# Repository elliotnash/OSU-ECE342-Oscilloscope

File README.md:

View this project on [CADLAB.io](https://cadlab.io/project/29860). 

# RustScope

A Dual Channel USB Oscilloscope designed for OSU ECE342 Junior Design 2

## Project Structure

- **`hardware/`** - Contains KiCad schematic and PCB design files for a RP2350 based oscilloscope board.

- **`firmware/`** - Rust firmware that runs on the oscilloscope board. Built using the Embassy async framework for embedded systems, targeting the RP2350 microcontroller. Handles ADC sampling / USB communication.

- **`client/`** - Tauri desktop application providing the oscilloscope user interface. Frontend built with React, TypeScript, and Tailwind CSS. Communicates with the firmware over USB to display waveforms and control oscilloscope settings.

- **`common/`** - Shared Rust crate containing models and (de)serialization logic used for communication between the firmware and Tauri application.

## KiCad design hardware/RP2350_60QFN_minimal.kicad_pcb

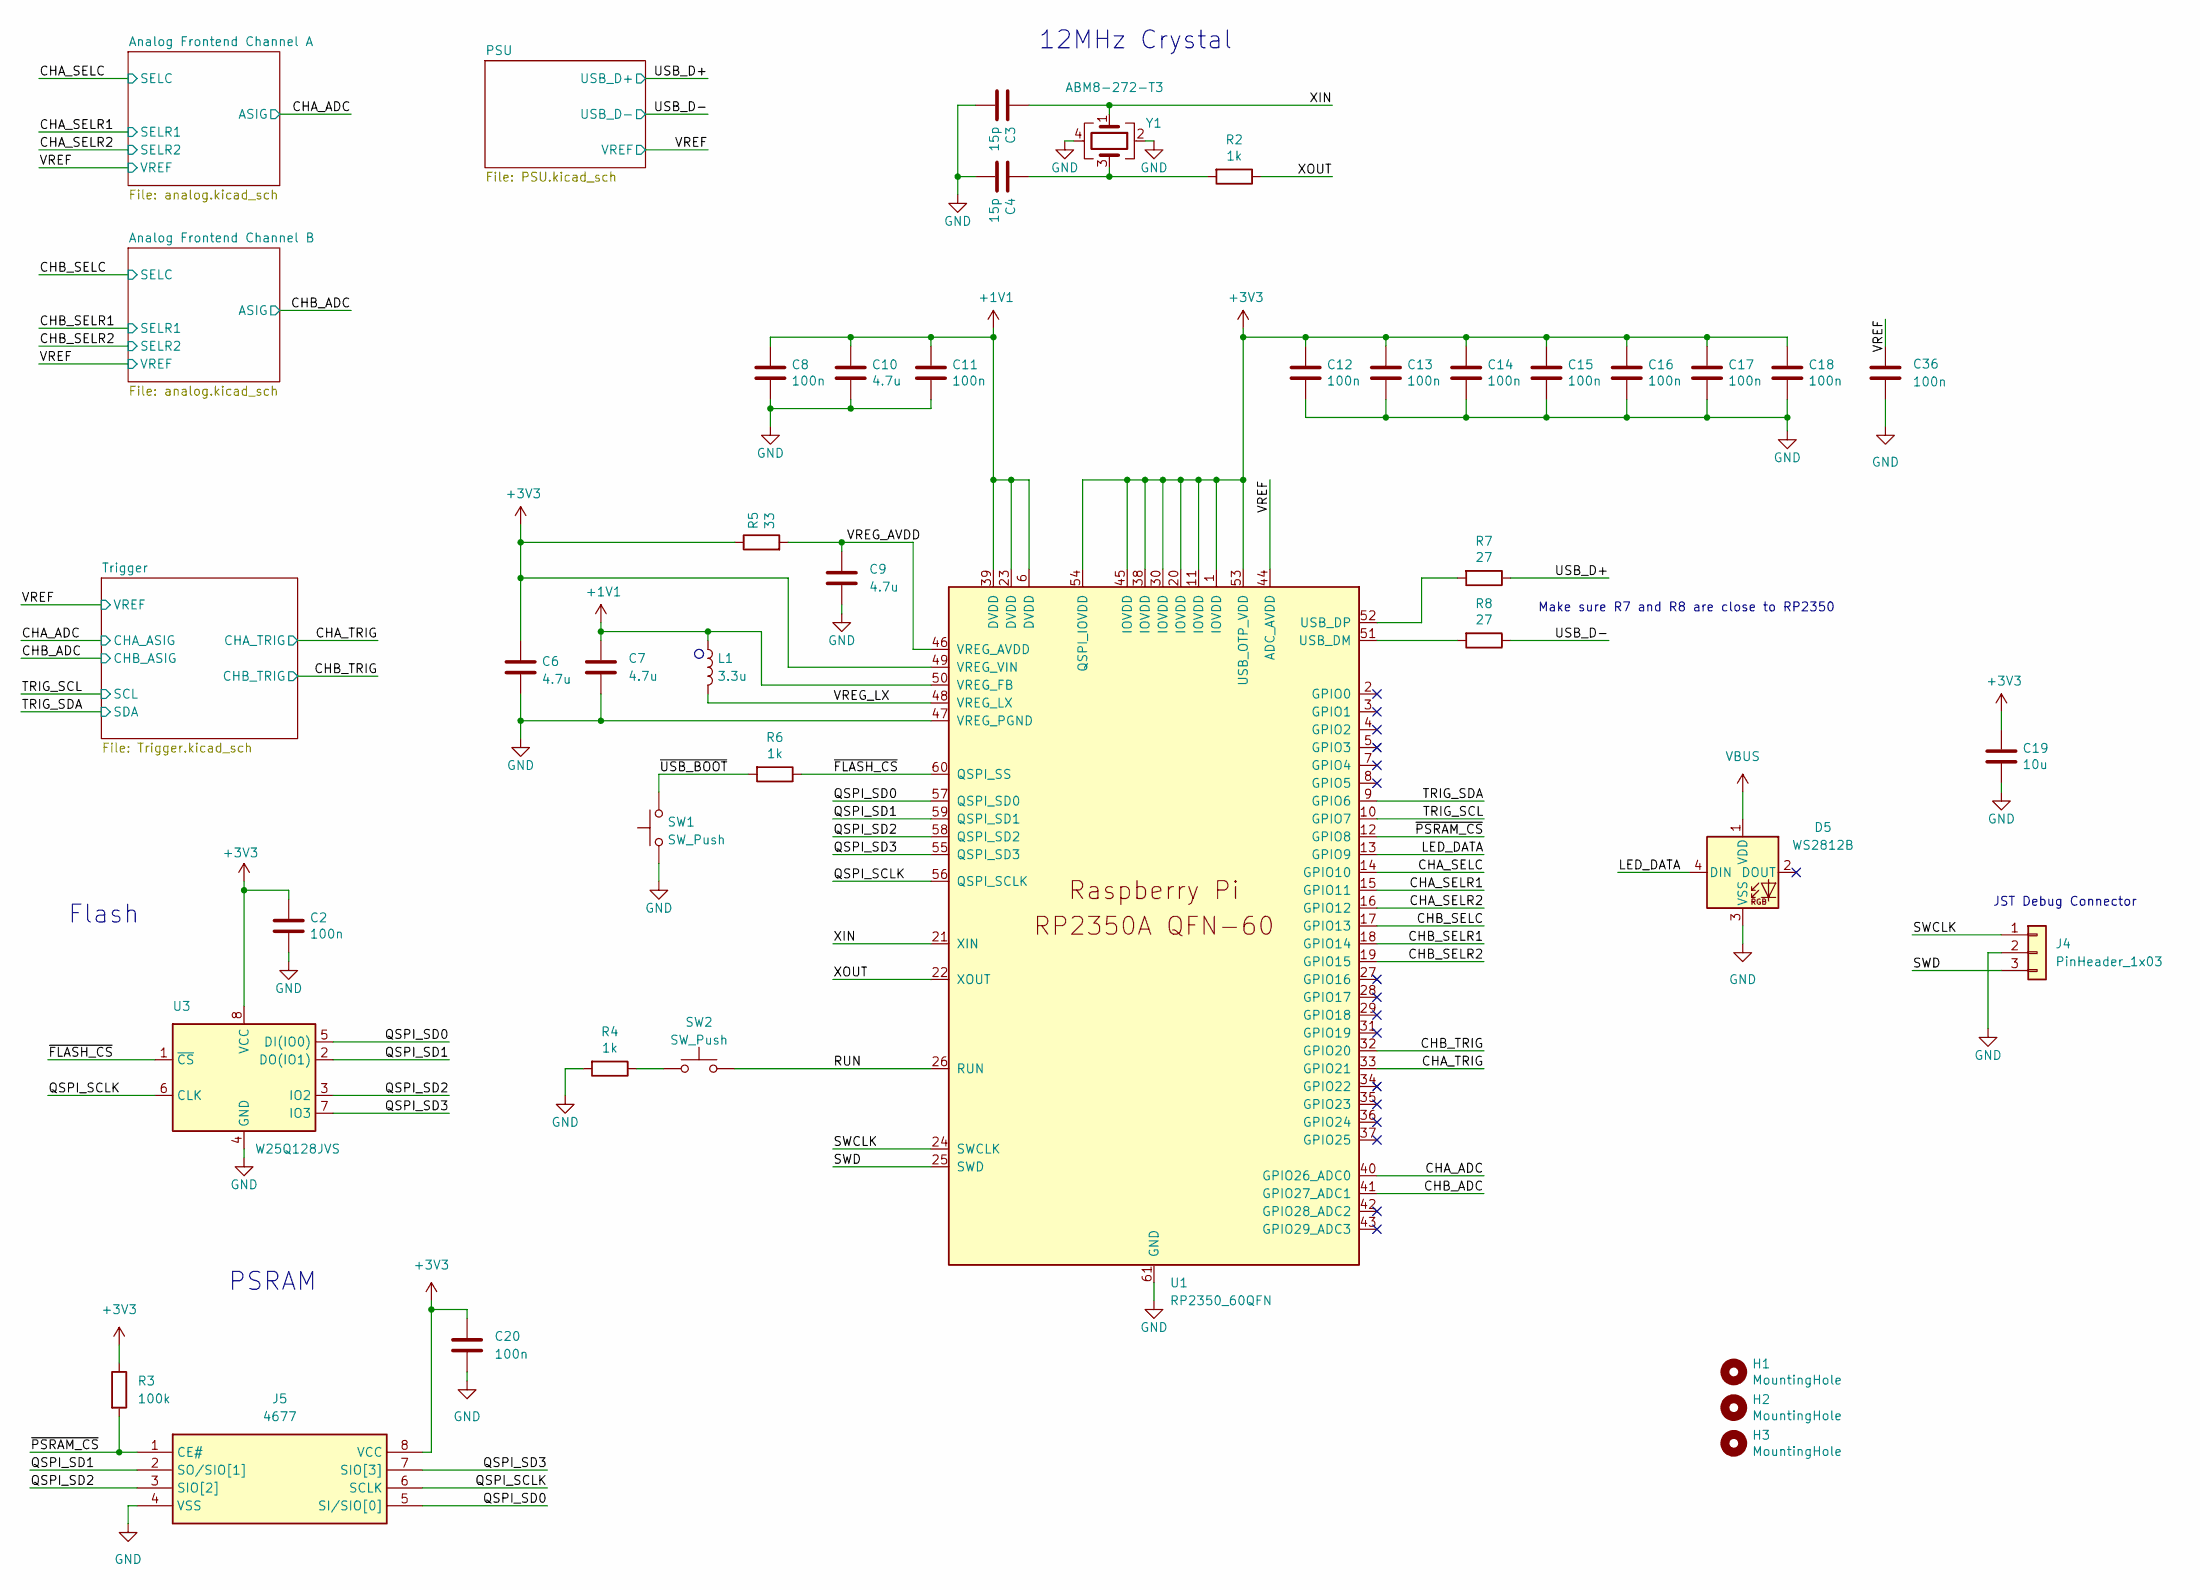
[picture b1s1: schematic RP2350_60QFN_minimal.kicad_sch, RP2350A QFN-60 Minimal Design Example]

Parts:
C2, C8, C11, C12, C13, C14, C15, C16, C17, C18, C20, C36: 100n; C_0402_1005Metric
C3, C4: 15p; C_0402_1005Metric
C6, C7: 4.7u; C_0402_1005Metric_small_pads
C9, C10: 4.7u; C_0402_1005Metric
C19: 10u; C_0805_2012Metric
D5: WS2812B; LED_WS2812B-Mini_PLCC4_3.5x3.5mm
H1, H2, H3: MountingHole; MountingHole_2.7mm_M2.5
J4: PinHeader_1x03; PinHeader_1x03_P2.54mm_Vertical
J5: 4677; SOIC127P600X175-8N; Mouser Part Number 485-4677
L1: 3.3u; L_pol_2016
R2, R4, R6: 1k; R_0402_1005Metric
R3: 100k; R_0402_1005Metric
R5: 33; R_0402_1005Metric
R7, R8: 27; R_0402_1005Metric
SW1, SW2: SW_Push; SW_TL3365AF180QG
U1: RP2350_60QFN; RP2350-QFN-60-1EP_7x7_P0.4mm_EP3.4x3.4mm_ThermalVias
U3: W25Q128JVS; SOIC-8_5.23x5.23mm_P1.27mm
Y1: ABM8-272-T3; Crystal_SMD_3225-4Pin_3.2x2.5mm

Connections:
+1V1: C7.1, C8.1, C10.1, C11.1, L1.1, U1.6 (DVDD), U1.23 (DVDD), U1.39 (DVDD), U1.50 (VREG_FB)
+3V3: C2.1, C6.1, C12.1, C13.1, C14.1, C15.1, C16.1, C17.1, C18.1, C19.1, C20.1, J5.8 (VCC), R3.1, R5.1, U1.1 (IOVDD), U1.11 (IOVDD), U1.20 (IOVDD), U1.30 (IOVDD), U1.38 (IOVDD), U1.45 (IOVDD), U1.49 (VREG_VIN), U1.53 (USB_OTP_VDD), U1.54 (QSPI_IOVDD), U3.8 (VCC); also elsewhere on the board
/CHA_ADC: U1.40 (GPIO26_ADC0); also elsewhere on the board
/CHA_SELC: U1.14 (GPIO10); also elsewhere on the board
/CHA_SELR1: U1.15 (GPIO11); also elsewhere on the board
/CHA_SELR2: U1.16 (GPIO12); also elsewhere on the board
/CHA_TRIG: U1.33 (GPIO21); also elsewhere on the board
/CHB_ADC: U1.41 (GPIO27_ADC1); also elsewhere on the board
/CHB_SELC: U1.17 (GPIO13); also elsewhere on the board
/CHB_SELR1: U1.18 (GPIO14); also elsewhere on the board
/CHB_SELR2: U1.19 (GPIO15); also elsewhere on the board
/CHB_TRIG: U1.32 (GPIO20); also elsewhere on the board
/LED_DATA: D5.4 (DIN), U1.13 (GPIO9)
/QSPI_SCLK: J5.6 (SCLK), U1.56 (QSPI_SCLK), U3.6 (CLK)
/QSPI_SD0: J5.5 (SI/SIO[0]), U1.57 (QSPI_SD0), U3.5 (DI(IO0))
/QSPI_SD1: J5.2 (SO/SIO[1]), U1.59 (QSPI_SD1), U3.2 (DO(IO1))
/QSPI_SD2: J5.3 (SIO[2]), U1.58 (QSPI_SD2), U3.3 (IO2)
/QSPI_SD3: J5.7 (SIO[3]), U1.55 (QSPI_SD3), U3.7 (IO3)
/RUN: SW2.2, U1.26 (RUN)
/SWCLK: J4.1, U1.24 (SWCLK)
/SWD: J4.3, U1.25 (SWD)
/TRIG_SCL: U1.10 (GPIO7); also elsewhere on the board
/TRIG_SDA: U1.9 (GPIO6); also elsewhere on the board
/USB_D+: R7.1; also elsewhere on the board
/USB_D-: R8.1; also elsewhere on the board
/VREF: C36.1, U1.44 (ADC_AVDD); also elsewhere on the board
/VREG_AVDD: C9.1, R5.2, U1.46 (VREG_AVDD)
/VREG_LX: L1.2, U1.48 (VREG_LX)
/XIN: C3.1, U1.21 (XIN), Y1.1
/XOUT: R2.1, U1.22 (XOUT)
/~FLASH_CS: R6.1, U1.60 (QSPI_SS), U3.1 (~CS)
/~PSRAM_CS: J5.1 (CE#), R3.2, U1.12 (GPIO8)
/~USB_BOOT: R6.2, SW1.2
GND: C2.2, C3.2, C4.2, C6.2, C7.2, C8.2, C9.2, C10.2, C11.2, C12.2, C13.2, C14.2, C15.2, C16.2, C17.2, C18.2, C19.2, C20.2, C36.2, D5.3 (VSS), J4.2, J5.4 (VSS), R4.2, SW1.1, U1.47 (VREG_PGND), U1.61 (GND), U3.4 (GND), Y1.2, Y1.4; also elsewhere on the board
unnamed: C4.1, R2.2, Y1.3
unnamed: R4.1, SW2.1
unnamed: R8.2, U1.51 (USB_DM)
unnamed: R7.2, U1.52 (USB_DP)
VBUS: D5.1 (VDD); also elsewhere on the board

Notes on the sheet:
JST Debug Connector
Flash
Make sure R7 and R8 are close to RP2350
PSRAM
12MHz Crystal

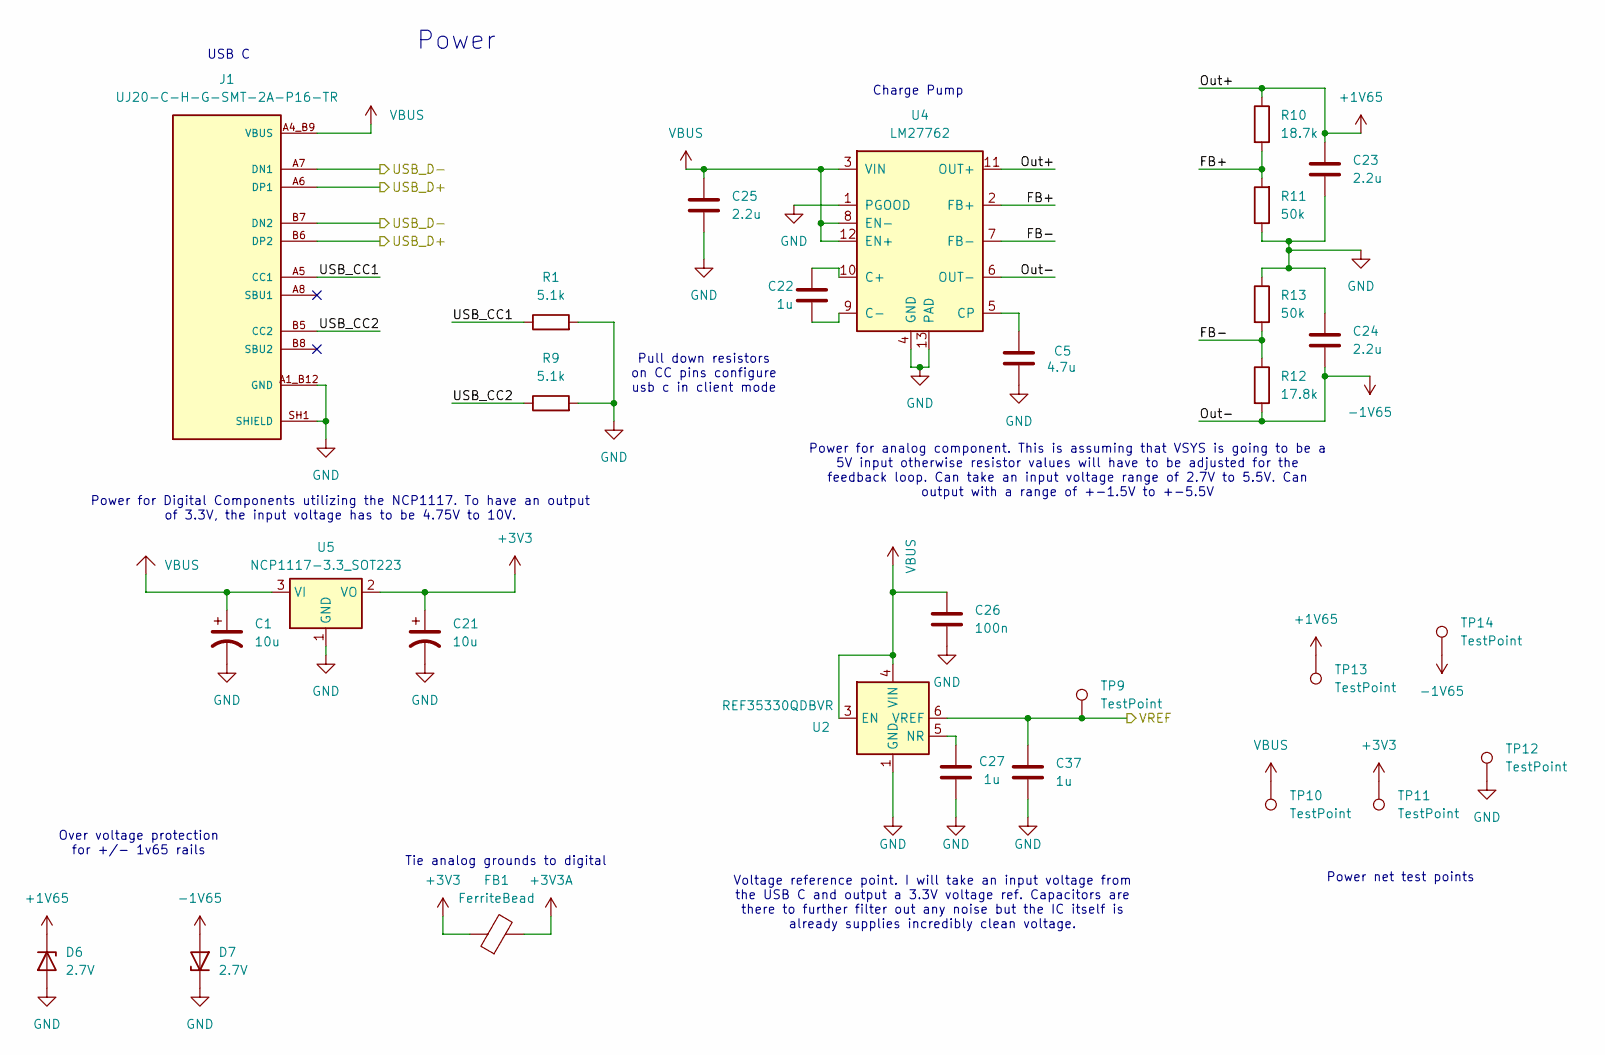
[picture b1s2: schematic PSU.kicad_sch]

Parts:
C1, C21: 10u; C_1206_3216Metric
C5: 4.7u; C_0402_1005Metric
C22, C27, C37: 1u; C_0402_1005Metric
C23, C24, C25: 2.2u; C_0402_1005Metric
C26: 100n; C_0402_1005Metric
D6, D7: 2.7V; D_SOD-123
FB1: FerriteBead; R_0603_1608Metric
J1: UJ20-C-H-G-SMT-2A-P16-TR; SAMESKY_UJ20-C-H-G-SMT-1-P16-TR; PARTREV 1.0
R1, R9: 5.1k; R_0402_1005Metric
R10: 18.7k; R_0402_1005Metric
R11, R13: 50k; R_0402_1005Metric
R12: 17.8k; R_0402_1005Metric
TP9, TP10, TP11, TP12, TP13, TP14: TestPoint; TestPoint_0603_1608Metric
U2: REF35330QDBVR; SOT-23-6
U4: LM27762; WSON-12-1EP_3x2mm_P0.5mm_EP1x2.65_ThermalVias
U5: NCP1117-3.3_SOT223; SOT-223-3_TabPin2

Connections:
+1V65: C23.1, D6.1 (K), R10.1, TP13.1, U4.11 (OUT+); also elsewhere on the board
+3V3: C21.1, FB1.1, TP11.1, U5.2 (VO); also elsewhere on the board
+3V3A: FB1.2; also elsewhere on the board
-1V65: C24.1, D7.2 (A), R12.2, TP14.1, U4.6 (OUT-); also elsewhere on the board
/PSU/FB+: R10.2, R11.2, U4.2 (FB+)
/PSU/FB-: R12.1, R13.2, U4.7 (FB-)
/PSU/USB_CC1: J1.A5 (CC1), R1.1
/PSU/USB_CC2: J1.B5 (CC2), R9.1
/USB_D+: J1.A6 (DP1), J1.B6 (DP2); also elsewhere on the board
/USB_D-: J1.A7 (DN1), J1.B7 (DN2); also elsewhere on the board
/VREF: C37.1, TP9.1, U2.6 (VREF); also elsewhere on the board
GND: C1.2, C5.2, C21.2, C23.2, C24.2, C25.2, C26.2, C27.1, C37.2, D6.2 (A), D7.1 (K), J1.A1_B12 (GND), J1.B1_A12 (GND), J1.SH1 (SHIELD), J1.SH2 (SHIELD), J1.SH3 (SHIELD), J1.SH4 (SHIELD), R1.2, R9.2, R11.1, R13.1, TP12.1, U2.1 (GND), U2.2 (GND), U4.1 (PGOOD), U4.4 (GND), U4.13 (PAD), U5.1 (GND); also elsewhere on the board
unnamed: C27.2, U2.5 (NR)
unnamed: C22.1, U4.10 (C+)
unnamed: C22.2, U4.9 (C-)
unnamed: C5.1, U4.5 (CP)
VBUS: C1.1, C25.1, C26.1, J1.A4_B9 (VBUS), J1.B4_A9 (VBUS), TP10.1, U2.3 (EN), U2.4 (VIN), U4.3 (VIN), U4.8 (EN-), U4.12 (EN+), U5.3 (VI); also elsewhere on the board

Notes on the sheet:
Pull down resistors on CC pins configure usb c in client mode
Charge Pump
USB C
Power for analog component. This is assuming that VSYS is going to be a 5V input otherwise resistor values will have to be adjusted for the feedback loop. Can take an input voltage range of 2.7V to 5.5V. Can output with a range of +-1.5V to +-5.5V
Power net test points
Power for Digital Components utilizing the NCP1117. To have an output of 3.3V, the input voltage has to be 4.75V to 10V.
Tie analog grounds to digital
Voltage reference point. I will take an input voltage from the USB C and output a 3.3V voltage ref. Capacitors are there to further filter out any noise but the IC itself is already supplies incredibly clean voltage.
Over voltage protection for +/- 1v65 rails
Power

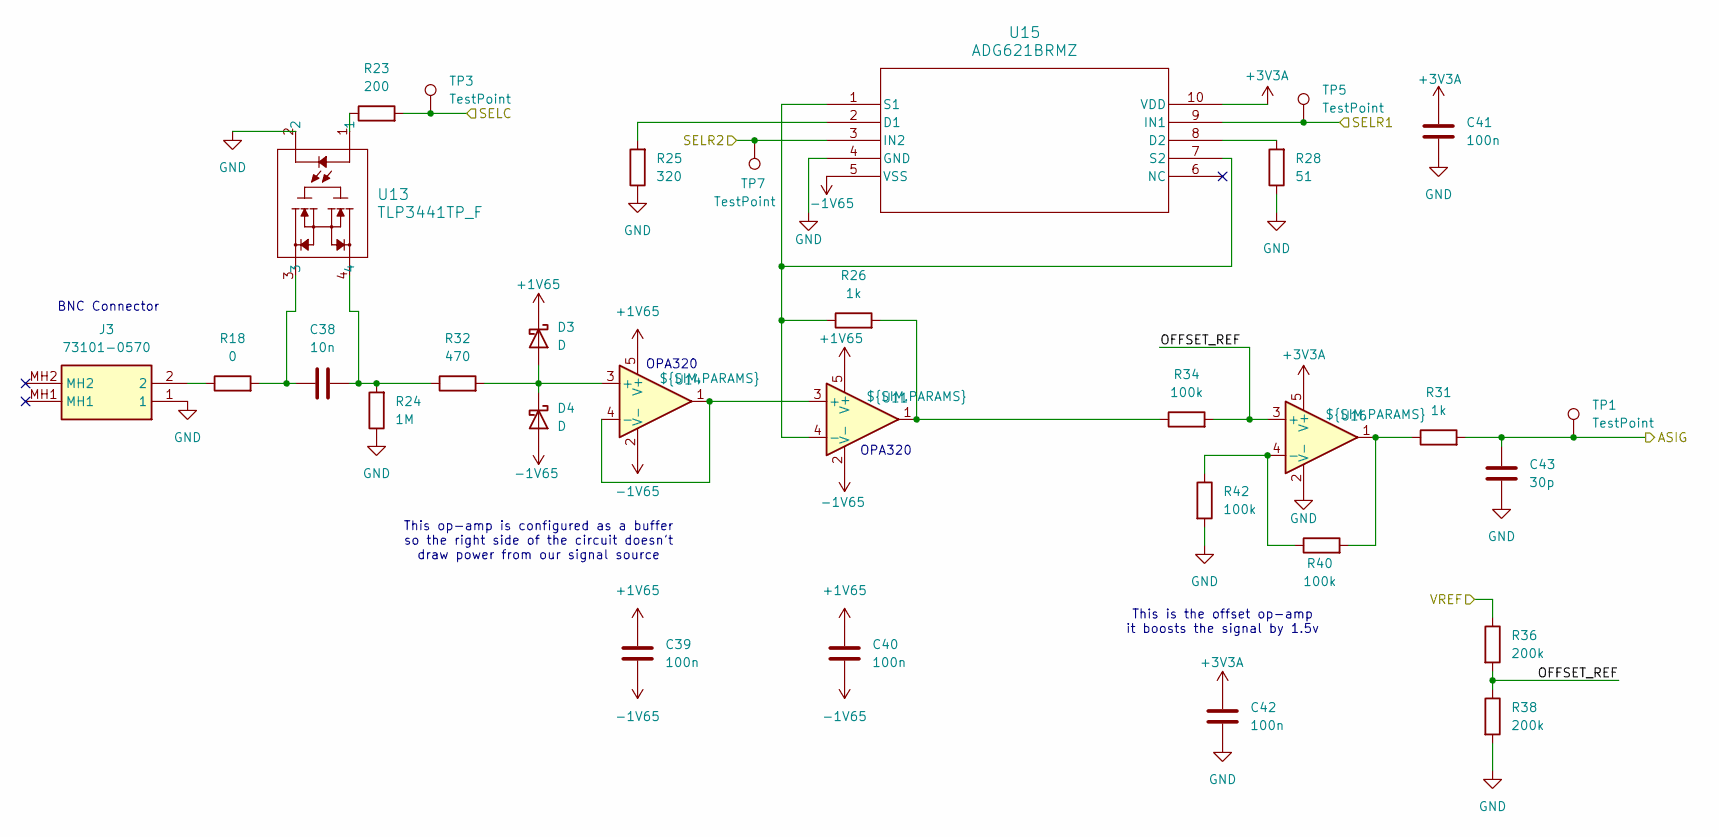
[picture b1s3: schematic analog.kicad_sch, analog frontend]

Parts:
C38: 10n; C_0402_1005Metric
C39, C40, C41, C42: 100n; C_0402_1005Metric
C43: 30p; C_0402_1005Metric
D3, D4: D; D_SOD-123
J3: 73101-0570; 731010570; Mouser Part Number 538-73101-0570
R18: 0; R_0603_1608Metric
R23: 200; R_0402_1005Metric
R24: 1M; R_0603_1608Metric
R25: 320; R_0603_1608Metric
R26, R31: 1k; R_0402_1005Metric
R28: 51; R_0603_1608Metric
R32: 470; R_0402_1005Metric
R34, R40, R42: 100k; R_0402_1005Metric
R36, R38: 200k; R_0402_1005Metric
TP1, TP3, TP5, TP7: TestPoint; TestPoint_0603_1608Metric
U11, U14, U16: ${SIM.PARAMS}; DBV5
U13: TLP3441TP_F; VSON4_TOS
U15: ADG621BRMZ; RM_10_ADI

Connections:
+1V65: C39.1, C40.1, D3.1 (K), U11.5 (V+), U14.5 (V+); also elsewhere on the board
+3V3A: C41.1, C42.1, U15.10 (VDD), U16.5 (V+); also elsewhere on the board
-1V65: C39.2, C40.2, D4.2 (A), U11.2 (V-), U14.2 (V-), U15.5 (VSS); also elsewhere on the board
/Analog Frontend Channel A/OFFSET_REF: R34.2, R36.2, R38.1, U16.3 (+)
/CHA_ADC: C43.1, R31.2, TP1.1; also elsewhere on the board
/CHA_SELC: R23.2, TP3.1; also elsewhere on the board
/CHA_SELR1: TP5.1, U15.9 (IN1); also elsewhere on the board
/CHA_SELR2: TP7.1, U15.3 (IN2); also elsewhere on the board
/VREF: R36.1; also elsewhere on the board
GND: C41.2, C42.2, C43.2, J3.1, R24.1, R25.1, R28.1, R38.2, R42.2, U13.2, U15.4 (GND), U16.2 (V-); also elsewhere on the board
unnamed: C38.1, R18.2, U13.3
unnamed: C38.2, R24.2, R32.1, U13.4
unnamed: D3.2 (A), D4.1 (K), R32.2, U14.3 (+)
unnamed: J3.2, R18.1
unnamed: R23.1, U13.1
unnamed: R26.2, R34.1, U11.1
unnamed: R31.1, R40.2, U16.1
unnamed: U11.3 (+), U14.1, U14.4 (-)
unnamed: R26.1, U11.4 (-), U15.1 (S1), U15.7 (S2)
unnamed: R25.2, U15.2 (D1)
unnamed: R28.2, U15.8 (D2)
unnamed: R40.1, R42.1, U16.4 (-)

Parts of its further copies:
C29: 10n; C_0402_1005Metric
C31, C32, C33, C34: 100n; C_0402_1005Metric
C35: 30p; C_0402_1005Metric
D1, D2: D; D_SOD-123
J2: 73101-0570; 731010570; Mouser Part Number 538-73101-0570
R14: 200; R_0402_1005Metric
R15: 1M; R_0603_1608Metric
R16: 320; R_0603_1608Metric
R17, R22: 1k; R_0402_1005Metric
R19: 51; R_0603_1608Metric
R20: 0; R_0603_1608Metric
R33: 470; R_0402_1005Metric
R35, R41, R43: 100k; R_0402_1005Metric
R37, R39: 200k; R_0402_1005Metric
TP2, TP4, TP6, TP8: TestPoint; TestPoint_0603_1608Metric
U8: TLP3441TP_F; VSON4_TOS
U10: ADG621BRMZ; RM_10_ADI

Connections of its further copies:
+1V65: C31.1, C32.1, D1.1 (K); also elsewhere on the board
+3V3A: C33.1, C34.1, U10.10 (VDD); also elsewhere on the board
-1V65: C31.2, C32.2, D2.2 (A), U10.5 (VSS); also elsewhere on the board
/Analog Frontend Channel B/OFFSET_REF: R35.2, R37.2, R39.1; also elsewhere on the board
/CHB_ADC: C35.1, R22.2, TP2.1; also elsewhere on the board
/CHB_SELC: R14.2, TP4.1; also elsewhere on the board
/CHB_SELR1: TP6.1, U10.9 (IN1); also elsewhere on the board
/CHB_SELR2: TP8.1, U10.3 (IN2); also elsewhere on the board
/VREF: R37.1; also elsewhere on the board
GND: C33.2, C34.2, C35.2, J2.1, R15.1, R16.1, R19.1, R39.2, R43.2, U8.2, U10.4 (GND); also elsewhere on the board
unnamed: C29.1, R20.2, U8.3
unnamed: C29.2, R15.2, R33.1, U8.4
unnamed 50: D1.2 (A), D2.1 (K), R33.2; also elsewhere on the board
unnamed: J2.2, R20.1
unnamed: R14.1, U8.1
unnamed 56: R17.2, R35.1; also elsewhere on the board
unnamed 57: R22.1, R41.2; also elsewhere on the board
unnamed: R16.2, U10.2 (D1)
unnamed: R19.2, U10.8 (D2)
unnamed 71: R17.1, U10.1 (S1), U10.7 (S2); also elsewhere on the board
unnamed 78: R41.1, R43.1; also elsewhere on the board

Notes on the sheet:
OPA320
BNC Connector
This op-amp is configured as a buffer so the right side of the circuit doesn't draw power from our signal source
This is the offset op-amp it boosts the signal by 1.5v

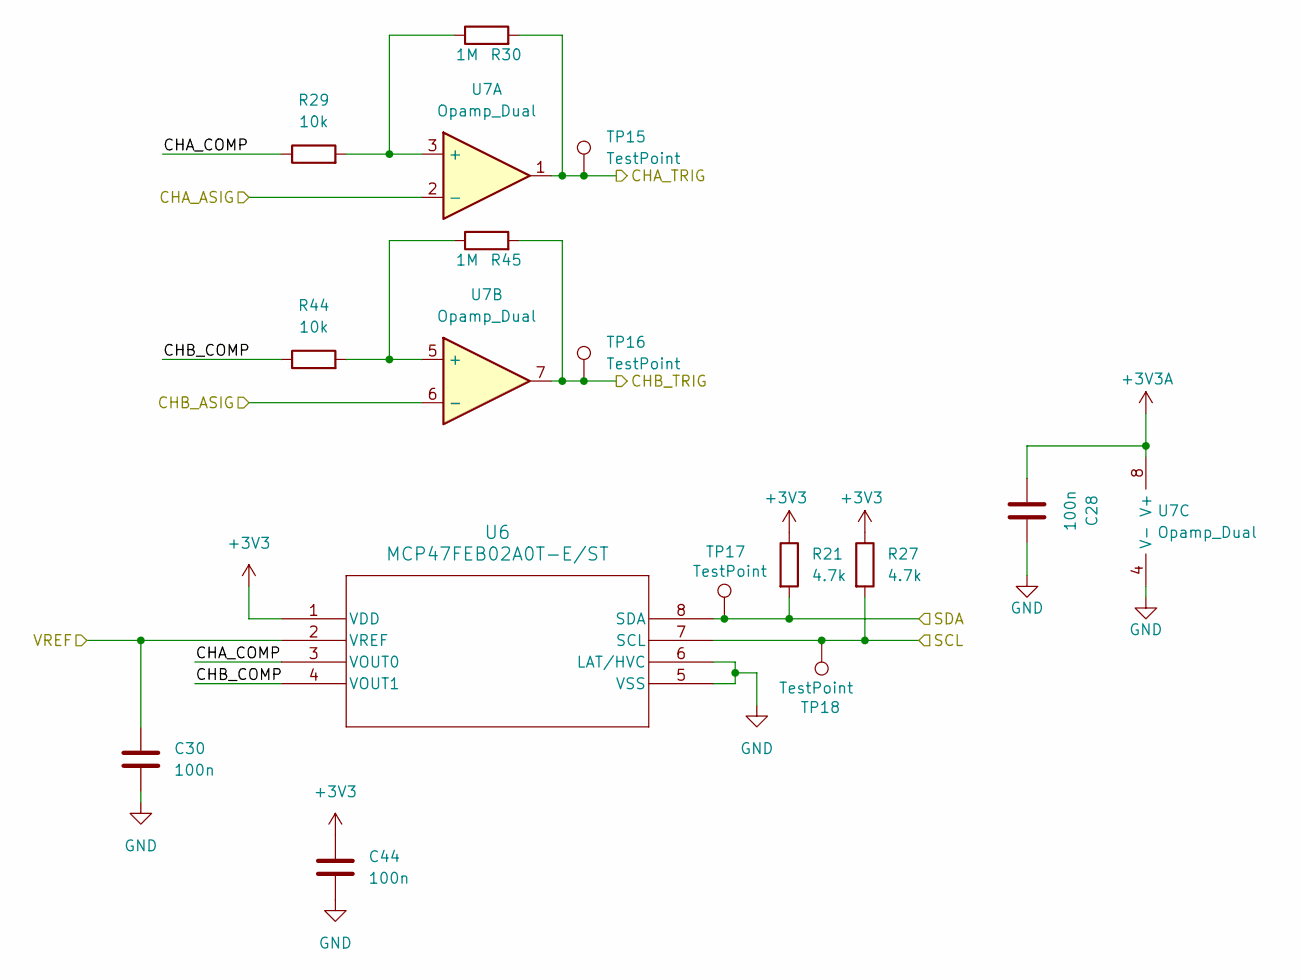
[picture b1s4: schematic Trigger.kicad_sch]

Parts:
C28, C30, C44: 100n; C_0402_1005Metric
R21, R27: 4.7k; R_0402_1005Metric
R29, R44: 10k; R_0402_1005Metric
R30, R45: 1M; R_0402_1005Metric
TP15, TP16, TP17, TP18: TestPoint; TestPoint_0603_1608Metric
U6: MCP47FEB02A0T-E/ST; TSSOP8_ST_MCH
U7: Opamp_Dual; SOIC127P600X175-8N

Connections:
+3V3: C44.2, R21.1, R27.1, U6.1 (VDD); also elsewhere on the board
+3V3A: C28.1, U7.8 (V+); also elsewhere on the board
/CHA_ADC: U7.2 (-); also elsewhere on the board
/CHA_TRIG: R30.2, TP15.1, U7.1; also elsewhere on the board
/CHB_ADC: U7.6 (-); also elsewhere on the board
/CHB_TRIG: R45.2, TP16.1, U7.7; also elsewhere on the board
/TRIG_SCL: R27.2, TP18.1, U6.7 (SCL); also elsewhere on the board
/TRIG_SDA: R21.2, TP17.1, U6.8 (SDA); also elsewhere on the board
/Trigger/CHA_COMP: R29.1, U6.3 (VOUT0)
/Trigger/CHB_COMP: R44.1, U6.4 (VOUT1)
/VREF: C30.2, U6.2 (VREF); also elsewhere on the board
GND: C28.2, C30.1, C44.1, U6.5 (VSS), U6.6 (LAT/HVC), U7.4 (V-); also elsewhere on the board
unnamed: R29.2, R30.1, U7.3 (+)
unnamed: R44.2, R45.1, U7.5 (+)

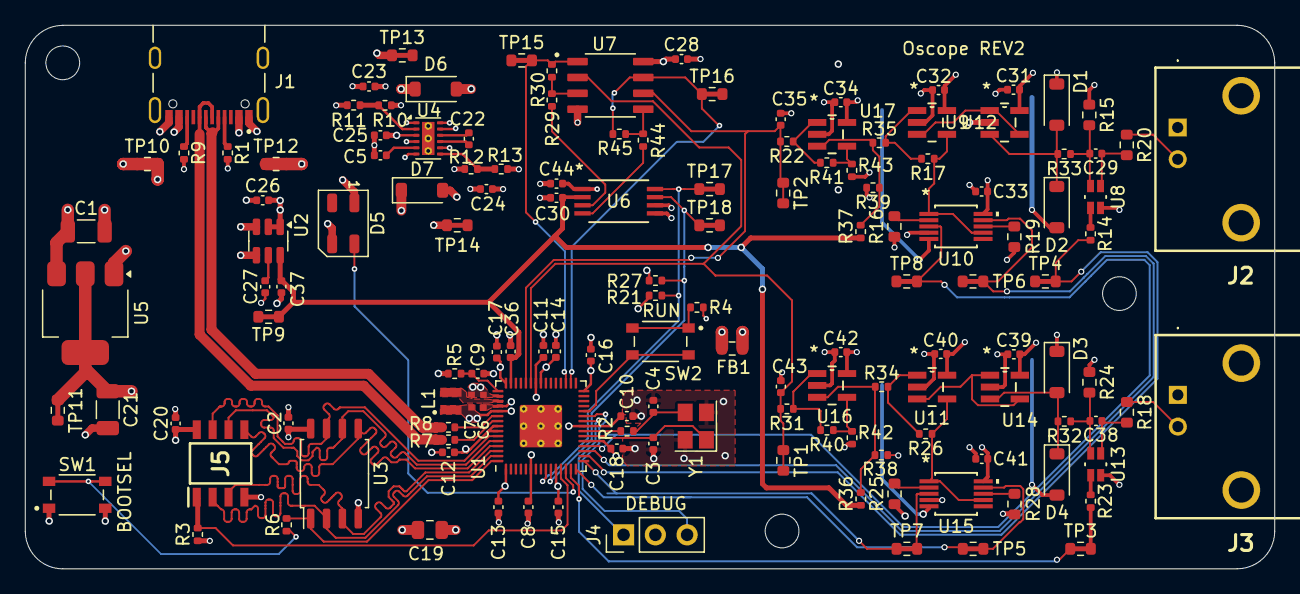
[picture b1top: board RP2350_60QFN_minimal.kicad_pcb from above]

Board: 4 copper layers, 100.0 x 43.5 mm, 144 parts (0 on the bottom side), 80 nets.

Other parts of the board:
U9, U12, U17: DBV5

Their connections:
+1V65: U9.5 (V+), U12.5 (V+); also elsewhere on the board
+3V3A: U17.5 (V+); also elsewhere on the board
-1V65: U9.2 (V-), U12.2 (V-); also elsewhere on the board
/Analog Frontend Channel B/OFFSET_REF: U17.3 (+); also elsewhere on the board
GND: U17.2 (V-); also elsewhere on the board
unnamed 50: U9.3 (+); also elsewhere on the board
unnamed 56: U12.1; also elsewhere on the board
unnamed 57: U17.1; also elsewhere on the board
unnamed 71: U12.4 (-); also elsewhere on the board
unnamed: U9.1, U9.4 (-), U12.3 (+)
unnamed 78: U17.4 (-); also elsewhere on the board

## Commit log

2026-01-16 feat: Initial per platform theming
2026-01-16 feat: Implement tauri logging
2026-01-18 Backlink to CADLAB.io has been added.
2026-01-18 replaced hardware folder with minimal simulation of rp2350
2026-01-19 feat(hardware): Add 8MB PSRAM Flash
2026-01-19 feat(hardware): Add USBC 1332645 library
2026-01-20 feat(hardware): Swap Micro USB with USB C
2026-01-20 feat(application): Prepare for move to main repository
2026-01-20 feat(client): Rename app->client
2026-01-20 feat(firmware,common): Initial firmware
2026-01-20 docs: Update readme
2026-01-20 ci(common): CI for common crate
2026-01-20 ci(common): Fix CI
2026-01-20 ci(common): Fix CI pt. 2
2026-01-20 ci(common): Update CI
2026-01-20 chore(common): Cargo fmt
2026-01-20 added digital psu
2026-01-20 added analog psu, needs review
2026-01-20 added links and prices
2026-01-21 feat(hardware): Move PSU to subschematic
2026-01-22 not done with Vref just saving for the night
2026-01-22 feat(client): Fix client builds, add CI builds
2026-01-22 ci(client): Add ubuntu dependencies
2026-01-22 ci(client): Update dependencies
2026-01-22 ci(client): Upload client bundle artifacts
2026-01-22 ci(client): Don't strip tauri builds
2026-01-22 added heirarchical labels for analog block
2026-01-22 updating
2026-01-22 merging stuff
2026-01-22 "Updated PSU, Updated spreadsheets
2026-01-23 finished part selection for analog/added photorelay switch for ac/dc coupling
2026-01-25 docs: Add initial docs
2026-01-25 docs: Update block diagram, add template for individual blocks
2026-01-26 feat(common): Add adaptive delta packing serializer for frame data
2026-01-26 feat(common): Refactor common crate
2026-01-26 fix(common): Fix improper absolute serialization of negative deltas
2026-01-26 chore(frontend,backend): Refactor client into backend/frontend directories, prepare to merge backend into cargo workspace
2026-01-26 ci(frontend,backend): Fix CI for client migration
2026-01-26 ci(application): Fix tauri cli install
2026-01-29 Up to date
2026-01-29 Trig
2026-01-29 added bnc foorptint and symbol
2026-01-29 Trig finished
2026-01-29 added decoupling capacitors to analog block
2026-01-29 updated trig
2026-01-30 connected analog i/o on main schematic and updated PSU naming
2026-01-31 feat(hardware): Cleanup schematic, replace offset stage with non-inverting op amp, add neopixel LED
2026-01-31 feat(hardware): Add charge pump over-voltage protection
2026-01-31 fix(hardware): Make power rail net naming consistent
2026-02-02 feat(frontend,backend): Migrate to IntentUI, update native colours
2026-02-02 feat(backend, frontend): Add support for platform titlebar controls
2026-02-02 chore(backend): Cargo fmt
2026-02-02 feat(hardware): Add zero ohm resistor before analog input
2026-02-03 feat(backend): Update linux theme
2026-02-03 updated psu
2026-02-04 updated spreadsheet
2026-02-04 added footprints
2026-02-04 feat(frontend): Add libadwaita style titlebar on linux
2026-02-04 feat(frontend): Add approximate macos traffic light buttons
2026-02-04 fix(frontend): Minor styling fixes
2026-02-05 feat(hardware): Add test point connections + update PCB layout
2026-02-05 feat(hardware): Update PCB layout for power and trigger blocks
2026-02-06 chore: Migrate to cargo workspace
2026-02-06 feat(test-firmware): Add initial USB-CDC test firmware
2026-02-06 feat(backend): Add serial port implementation
2026-02-06 feat(backend,frontend): Migrate to tanstack router, add USB connection logic in frontend
2026-02-07 feat(backend,frontend): Working mcu<->backend comm
2026-02-07 feat(backend): Use tokio channel for status
2026-02-07 feat(hardware): Organize MCU block layout
2026-02-07 feat(hardware): Fix disconnected analog block pins
2026-02-07 feat(hardware): Update switch footprint
2026-02-07 feat(hardware): Layout analog block 1
2026-02-07 feat(hardware): Finish component layout
2026-02-07 feat(hardware): updted design rules
2026-02-08 feat(hardware): Route mcu
2026-02-08 feat(hardware): Add VBUS plane
2026-02-08 feat(hardware): Janky flash QSPI length matching
2026-02-08 feat(hardware): PSRAM length matching
2026-02-08 feat(hardware): Add 1v65 rail on 4th plane
2026-02-08 feat(hardware): Add fill zones for 1v65 rails, route charge pump
2026-02-08 feat(hardware): Connect bottom layer data lines
2026-02-08 feat(hardware): Route USB data differential pair
2026-02-08 ci: remove action rustfmt
2026-02-08 feat(hardware): Cleanup power routes
2026-02-08 ci: Add new system dependencies
2026-02-08 feat(hardware): Update 1v65 fill
2026-02-08 routed analog block
2026-02-08 fixed vref routing and -1v65 for CHA switch
2026-02-09 feat(hardware): Fix unconnected nets
2026-02-09 fix(hardware): Fix pad clearances
2026-02-09 fix(hardware): Fix misc. DRC warnings
2026-02-09 feat(hardware): Add rear silkscreen
2026-02-09 fix(hardware): Update minimum via size
2026-02-09 feat(hardware): Misc changes
2026-02-09 docs(hardware): Add offset resistor tolerances to bom
2026-02-10 feat(hardware): Add 3d models for all components
2026-02-13 feat(hardware): Update RP2350 3d model
2026-02-13 feat(frontend): Add initial waveform plot with visx
2026-02-13 feat(common, frontend): Update framedata struct, mock wavefrom from framedata
2026-02-13 feat(frontend): Add homepage sidebar
2026-02-13 feat(frontend): Add status panel
2026-02-14 feat(frontend): Add statistics bar under waveform
2026-02-14 fix(test-firmware): Split frames into 64 byte usb cdc packets
2026-02-15 feat(frontend): Add plot origin line, use css vars for grid colours
2026-02-15 feat(frontend): Add additional IntentUI components, rework titlebar
2026-02-15 feat(frontend): Add channel controls
2026-02-16 feat(frontend): Add math channel controls
2026-02-16 fix(frontend): Fix channel naming in math presets
2026-02-16 feat(frontend): Initial echarts migration
2026-02-16 feat(frontend): Clean up echarts styling
2026-02-16 fix(frontend): Fix incorrect marker colour
2026-02-17 feat(common): Add channel control option messages
2026-02-17 feat(test-firmware): Add receive loop
2026-02-17 feat(test-firmware): Use embassy tasks to manage USB sending
2026-02-17 fix(test-firmware): Fix import conflicts, use seperate channel sender for dummy frames
2026-02-17 fix(test-firmware): Increase heap size to prevent allocation failures
2026-02-18 Use embassy_sync Watch instead of Channel to ensure only current data is sent
2026-02-18 feat(firmware): Copy test-firmware to firmware crate for initial firmware implementation
2026-02-18 feat(firmware, test-firmware): Refactor firmware, fix all cargo warnings
2026-02-21 changed pcb size, added pull up resistors to I2C, fixed OPA320 footprints/schematic
2026-02-21 feat(firmware): Seperate memory.x layout for rp2040 and rp2350
2026-02-21 feat(firmware): Add bitbanged i2c implementation to test dac with incorrect pin config
2026-02-21 fix(hardware): Fix swapped i2c pins
2026-02-21 feat(hardware): Add 30mV hysteresis to trigger
2026-02-21 fix(hardware): Fix neopixel footprint size
2026-02-21 fix(hardware): Fix routing issues
2026-02-21 feat(hardware): Update silkscreen
2026-02-24 feat(hardware): Finalize REV2
2026-02-24 feat(firmware): Implement embedded hal async i2c trait for bitbanged i2c
2026-02-24 fix(common): Fix incorrect decoding of negative deltas
2026-02-24 feat(firmware,common): Add trigger messages and implement ADC frame sending
2026-02-24 fix(backend): Don't panic on message parse failure
2026-02-24 fix(firmware): Don't drop frames sent at the same time
2026-02-26 changed mcu-test to set GPIO pins high and send GPIO input through tunnel via message
2026-02-26 feat(trigger-test-firmware): Initial trigger test firmware
2026-02-26 fix(firmware): Fix DAC initialization
2026-02-26 feat(frontend, common): Add test panel verification messages
2026-02-26 feat(all): Implement verfication messages in frontend, add dac test protocol
2026-02-26 feat(firmware,backend): Buffer DAC vref, temp fix for data encoding
2026-02-26 fix(all): FIx backend to frontend data connection
2026-02-26 feat(frontend): Add both channels on graph, pull from serialized data
2026-02-26 feat(frontend): Add fps counter
2026-02-26 mcu-test-firmware stuff
2026-02-26 feat(frontend): Implement channel enable switches
2026-02-26 feat(frontend): Implement 10x attenuation
2026-02-26 feat(frontend): Implement math channel
2026-03-01 feat(hardware): Update opa320 3d models
2026-03-02 feat(firmware): Add neopixel support
2026-03-03 feat(firmware): Refactor LED task, add options for led patterns, and set patterns based on firmware state
2026-03-03 feat(backend): Implement heartbeat sending/receiving on backend
2026-03-03 fix(frontend): Fix tooltip dissapearing
2026-03-03 fix(frontend): Fully hide series symbol in tooltip
2026-03-03 fix(frontend): Fix channels not being removed once off
2026-03-03 fix(frontend): Remove symbol from math channel
2026-03-04 feat(firmware): Remove bitbanged i2c for REV2
2026-03-04 fix(frontend): Implement dynamic buffer for receiving messages to ensure incomplete messages aren't parsed
2026-03-05 feat(firmware): Implement firmware channel options/sampling rate
2026-03-05 chore: Clean up unused projects
2026-03-05 feat(firmware): Add NVS property store for calibration data
2026-03-05 feat(firmware): Implement usb calibration message
2026-03-06 feat(firmware): Update calibration logic
2026-03-06 feat(frontend): Move auto scale functionality to auto scale button
2026-03-06 feat(firmware): Implement multi core ADC reading
2026-03-06 feat(frontend): Add voltage scale sliders
2026-03-06 feat(firmware): Add trigger options watch
2026-03-06 feat(frontend): Limit auto scale to voltage_scale/20
2026-03-06 feat(frontend): Stats bar
2026-03-06 feat(frontend): Add time range slider
2026-03-06 fix(frontend): Fix viewport moving when changing sample rate
2026-03-06 feat(firmware): Cleanup NVS, use watch for commmunication and macros to simplify flash layout
2026-03-09 feat(firmware, backend): Implement trigger block
2026-03-09 feat(frontend,backend): Implement native macos window controls
2026-03-10 fix(frontend): Fix waveform chart not resizing on window resize
2026-03-10 feat(frontend): Show toast when placing trigger
2026-03-10 chore: version++
2026-03-10 fix(backend): Fix backend build on non-macos platforms
2026-03-10 fix(backend): Don't clone serial port, fixes OS error on windows
2026-03-10 feat(frontend): Implement native looking windows controls
2026-03-10 feat(frontend): Refactor windows titlebar controls
2026-03-10 chore(frontend): Cleanup unused backend code
2026-03-10 fix(frontend): Fix macos menu button styling
2026-03-10 chore: Actually bump version this time
2026-03-10 feat(backend): Use native serial split on unix based OS
2026-03-10 fix(frontend): Fix serial connection on linux
2026-03-10 feat(frontend): Update linux style
2026-03-10 chore: Remove simple-firmware
2026-03-10 ci: Add macos builds
2026-03-10 fix: Remove unused firmware
2026-03-10 docs: Update image
2026-03-12 docs: Update final (ish) docs
2026-03-31 chore: Update description
